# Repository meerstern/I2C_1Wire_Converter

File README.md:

# I2C-1Wireマスタ変換基板
I2C_1Wire_Converter with DS2485

## 概要
  * [DS2485][1]とレベル変換回路を搭載したI2C-1Wireマスタ変換基板です  
  * I2Cスレーブを1Wireマスタに変換します  
  * タイミングがシビアな1WireデバイスをI2Cコマンドで容易に操作することが可能です  
  * DS2485のレジスタを変更することで1Wire通信のタイミングを細かく調整することが可能です  
  * DS2485は126バイトのバッファを備えており、効率良く1Wire通信をすることが可能です  
  * 本変換基板にはレベル変換回路を搭載しているため、5VレベルのI2C及び1Wireに対応しています  
  * DS2485のGPIOは電源入力のPchMOSFETに接続されています  
  * 電源入力のPchMOSFETを介して1Wireバスの強力プルアップを利用することが可能です  
  * I2Cの接続はGrove互換コネクタを使用しています  
  * 1Wireの接続はVCC、1Wire、GNDの2.54mmピッチターミナルコネクタを使用しています  
  * 1Wireの電源及び信号電圧レベルはGroveコネクタから供給する電源電圧に一致します  
  * 電源電圧：3.3V~5V
  * 基板サイズ25mm x30mm、固定穴M3x2 幅19mm
  
 ## 販売サイト
  * [スイッチサイエンス][2]

[1]: https://www.maximintegrated.com/jp/products/ibutton-one-wire/memory-products/DS2485.html
[2]: https://www.switch-science.com/products/8650

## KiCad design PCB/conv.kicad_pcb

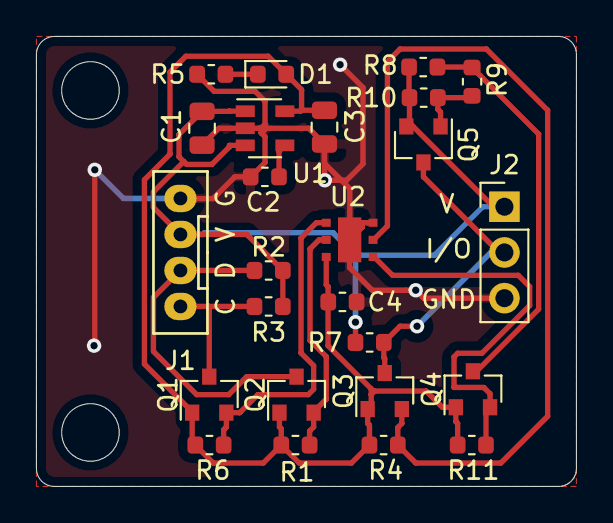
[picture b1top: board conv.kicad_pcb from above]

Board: 2 copper layers, 30.0 x 25.0 mm, 27 parts (0 on the bottom side), 14 nets.

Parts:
C1, C3: 10u; C_0805_2012Metric
C2: 0.01u; C_0603_1608Metric
C4: 0.1u; C_0603_1608Metric
D1: LED; LED_0603_1608Metric
J1: Conn_01x04; GROVE
J2: Conn_01x03; PinHeader_1x03_P2.54mm_Vertical
Q1, Q2, Q3, Q4: Q_NMOS_GSD; SOT-23
Q5: Q_PMOS_GSD; SOT-23
R1, R2, R3, R6, R10: 10k; R_0603_1608Metric
R4, R7, R8, R11: 4.7k; R_0603_1608Metric
R5, R9: 1k; R_0603_1608Metric
REF1, REF2: MountingHole_3.2mm_M3
U1: LD3985M33R_SOT23; SOT-23-5
U2: ds2485; TDFN6-EP

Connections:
+3V3: C3.1, C4.1, D1.2, Q1.1, Q2.1, Q3.1, Q4.1, R1.1, R4.1, R6.1, R11.1, U1.5, U2.6
/GPIO: Q4.2, R11.2, U2.1
/GPIO_H: Q4.3, R8.2, R9.2
/IO: Q3.2, R4.2, U2.2
/IO_H: J2.2, Q3.3, Q5.3, R7.2
/SCL: Q1.2, R6.2, U2.4
/SCL_H: J1.1, Q1.3, R3.2
/SDA: Q2.2, R1.2, U2.5
/SDA_H: J1.2, Q2.3, R2.2
/VIN: C1.1, J1.3, J2.1, Q5.2, R2.1, R3.1, R7.1, R8.1, R10.1, U1.1, U1.3
GND: C1.2, C2.2, C3.2, C4.2, J1.4, J2.3, R5.2, U1.2, U2.3, U2.7
unnamed: C2.1, U1.4
unnamed: D1.1, R5.1
unnamed: Q5.1, R9.1, R10.2

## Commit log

2022-11-15 Add images
2022-11-17 Add Sample Code
2022-11-17 Add PCB
2022-12-06 Add shop link
2023-04-06 Fix DS18B20 code
